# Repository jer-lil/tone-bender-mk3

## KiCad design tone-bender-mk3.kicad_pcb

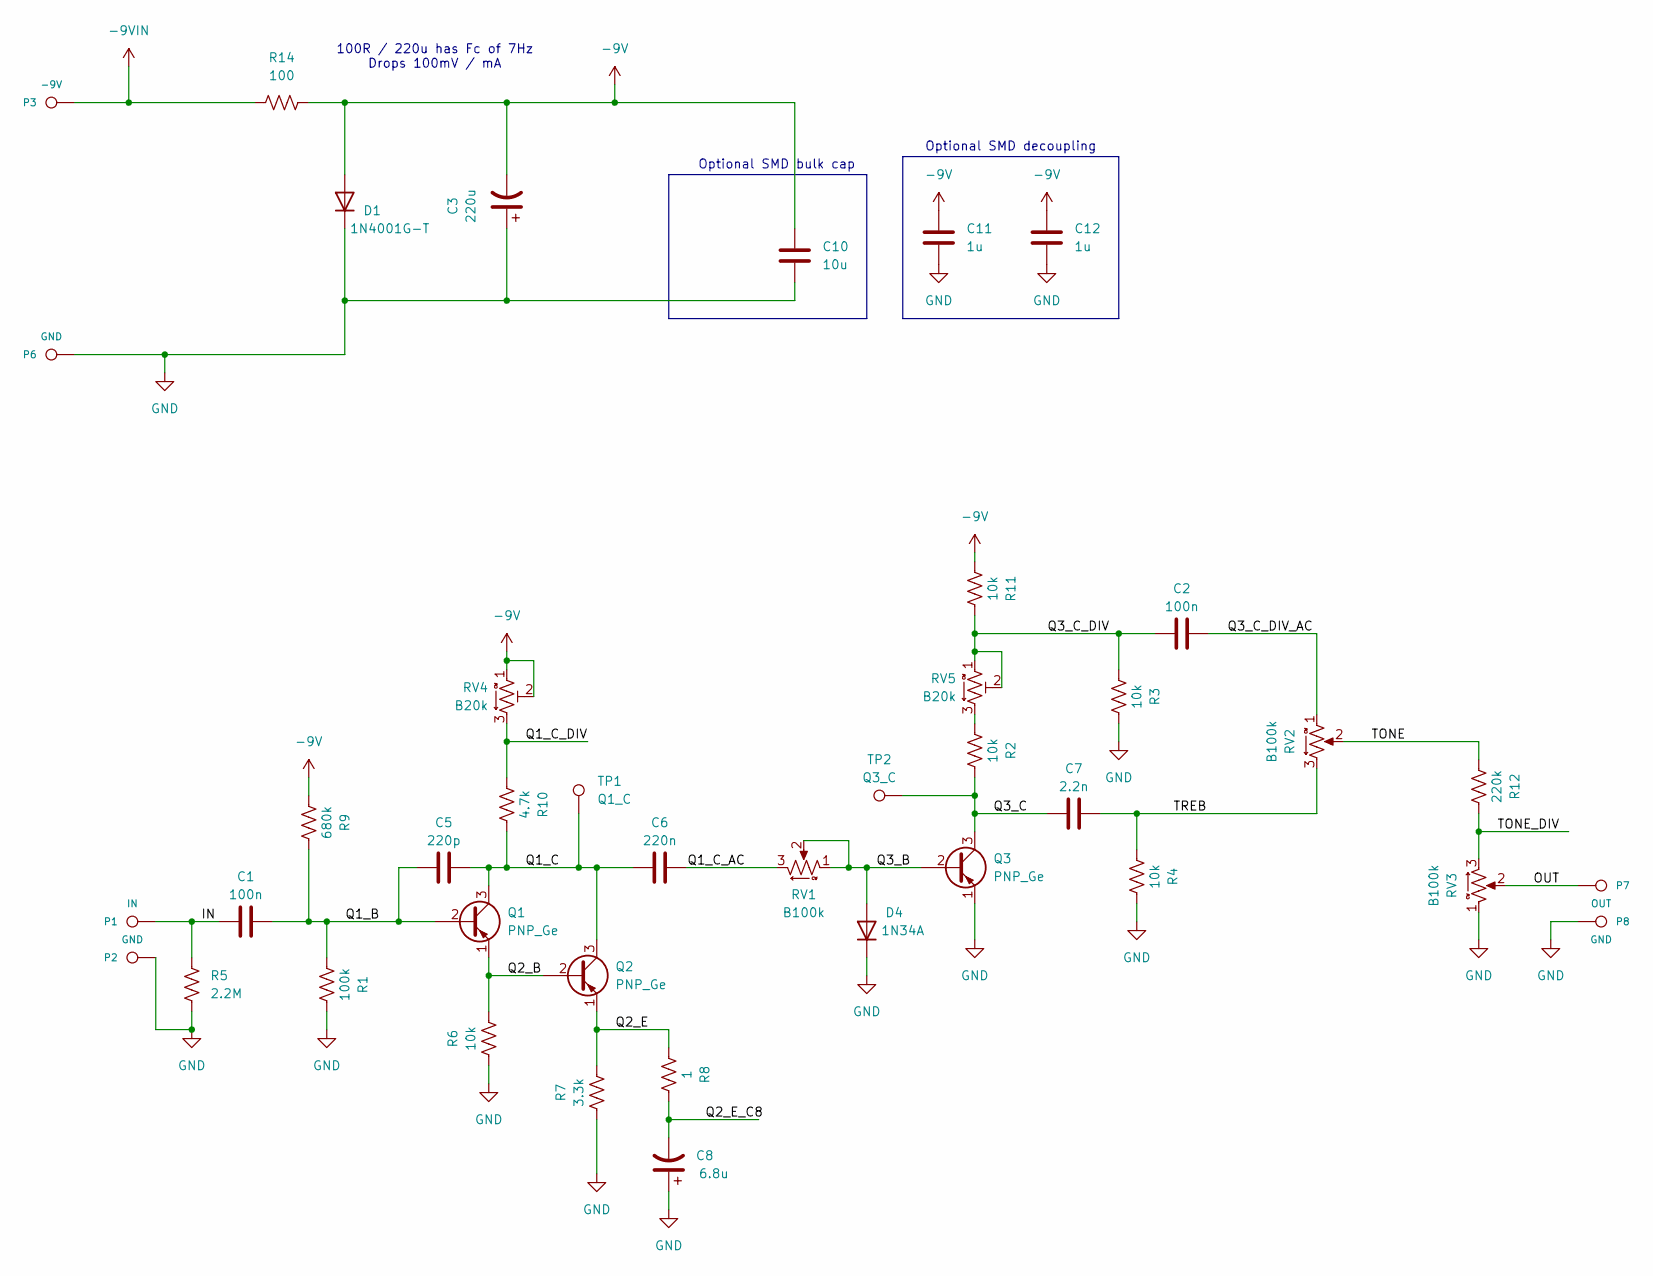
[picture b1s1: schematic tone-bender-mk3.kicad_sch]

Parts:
C1, C2: 100n; C_Rect_L7.2mm_W5.5mm_P5.00mm_FKS2_FKP2_MKS2_MKP2; Tolerance 20%
C3: 220u; CP_Radial_D8.0mm_P3.50mm
C5: 220p; C_Rect_L7.2mm_W4.5mm_P5.00mm_FKS2_FKP2_MKS2_MKP2; Tolerance 20%
C6: 220n; C_Rect_L7.2mm_W3.0mm_P5.00mm_FKS2_FKP2_MKS2_MKP2; Tolerance 20%
C7: 2.2n; C_Rect_L7.2mm_W4.5mm_P5.00mm_FKS2_FKP2_MKS2_MKP2; Tolerance 20%
C8: 6.8u; CP_Radial_D5.0mm_P2.50mm
C10: 10u; C_2220_5750Metric_Pad1.97x5.40mm_HandSolder
C11, C12: 1u; C_0805_2012Metric_Pad1.18x1.45mm_HandSolder
D1: 1N4001G-T; D_DO-41_SOD81_P7.5mm_Horizontal; Voltage 1V @ 1A; MPN 1N4001G-T
D4: 1N34A; D_DO-41_SOD81_P10.0mm_Horizontal; Voltage 0.3V; MPN 1N34A
P1: IN; WirePad_22AWG
P2, P6, P8: GND; WirePad_22AWG
P3: -9V; WirePad_22AWG
P7: OUT; WirePad_22AWG
Q1, Q2, Q3: PNP_Ge; TO-92L_Wide_EBC; MPN PNP_Ge
R1: 100k; R_Axial_DIN0207_L6.3mm_D2.5mm_P7.5mm_Horizontal
R2, R3, R4, R6, R11: 10k; R_Axial_DIN0207_L6.3mm_D2.5mm_P7.5mm_Horizontal
R5: 2.2M; R_Axial_DIN0207_L6.3mm_D2.5mm_P7.5mm_Horizontal
R7: 3.3k; R_Axial_DIN0207_L6.3mm_D2.5mm_P7.5mm_Horizontal
R8: 1; R_Axial_DIN0207_L6.3mm_D2.5mm_P7.5mm_Horizontal
R9: 680k; R_Axial_DIN0207_L6.3mm_D2.5mm_P7.5mm_Horizontal
R10: 4.7k; R_Axial_DIN0207_L6.3mm_D2.5mm_P7.5mm_Horizontal
R12: 220k; R_Axial_DIN0207_L6.3mm_D2.5mm_P7.5mm_Horizontal
R14: 100; R_Axial_DIN0207_L6.3mm_D2.5mm_P7.5mm_Horizontal
RV1, RV2, RV3: B100k; Potentiometer_16MM
RV4, RV5: B20k; Potentiometer_Bourns_3362P_Vertical; MPN 3362P-1-203LF
TP1: Q1_C; TestPoint_Keystone_5000-5004_Miniature
TP2: Q3_C; TestPoint_Keystone_5000-5004_Miniature

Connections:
-9V: C3.2, C10.1, C11.1, C12.1, D1.2 (A), R9.2, R11.2, R14.2, RV4.1, RV4.2
-9VIN: P3.1, R14.1
/IN: C1.1, P1.1, R5.1
/OUT: P7.1, RV3.2
/Q1_B: C1.2, C5.1, Q1.2 (B), R1.2, R9.1
/Q1_C: C5.2, C6.1, Q1.3 (C), Q2.3 (C), R10.1, TP1.1
/Q1_C_AC: C6.2, RV1.3
/Q1_C_DIV: R10.2, RV4.3
/Q2_B: Q1.1 (E), Q2.2 (B), R6.1
/Q2_E: Q2.1 (E), R7.1, R8.2
/Q2_E_C8: C8.2, R8.1
/Q3_B: D4.2 (A), Q3.2 (B), RV1.1, RV1.2
/Q3_C: C7.1, Q3.3 (C), R2.1, TP2.1
/Q3_C_DIV: C2.1, R3.2, R11.1, RV5.1, RV5.2
/Q3_C_DIV_AC: C2.2, RV2.1
/TONE: R12.2, RV2.2
/TONE_DIV: R12.1, RV3.3
/TREB: C7.2, R4.2, RV2.3
GND: C3.1, C8.1, C10.2, C11.2, C12.2, D1.1 (K), D4.1 (K), P2.1, P6.1, P8.1, Q3.1 (E), R1.1, R3.1, R4.1, R5.2, R6.2, R7.2, RV3.1
unnamed: R2.2, RV5.3

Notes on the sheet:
100R / 220u has Fc of 7Hz Drops 100mV / mA
Optional SMD bulk cap
Optional SMD decoupling

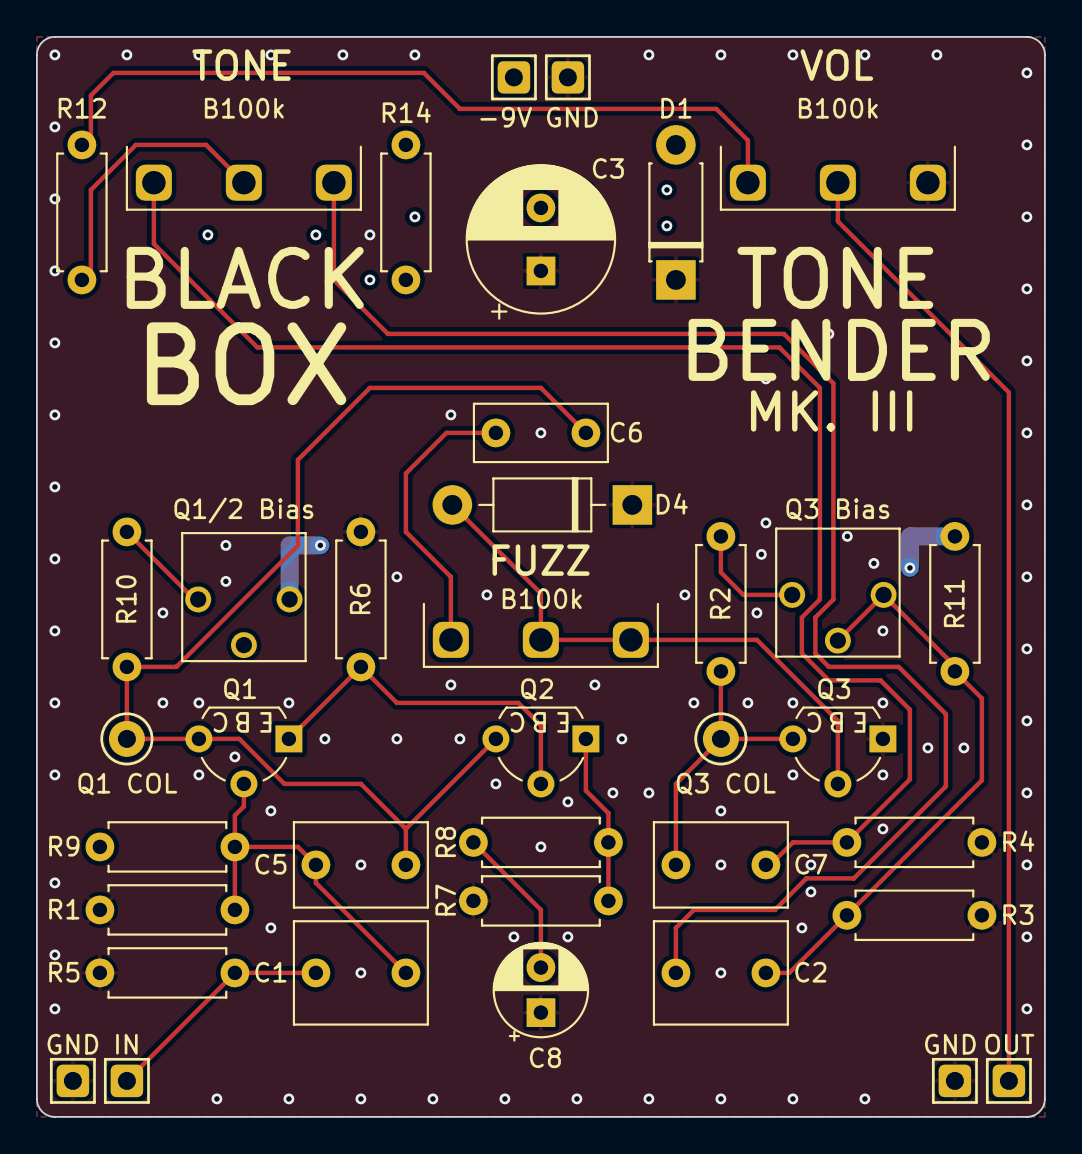
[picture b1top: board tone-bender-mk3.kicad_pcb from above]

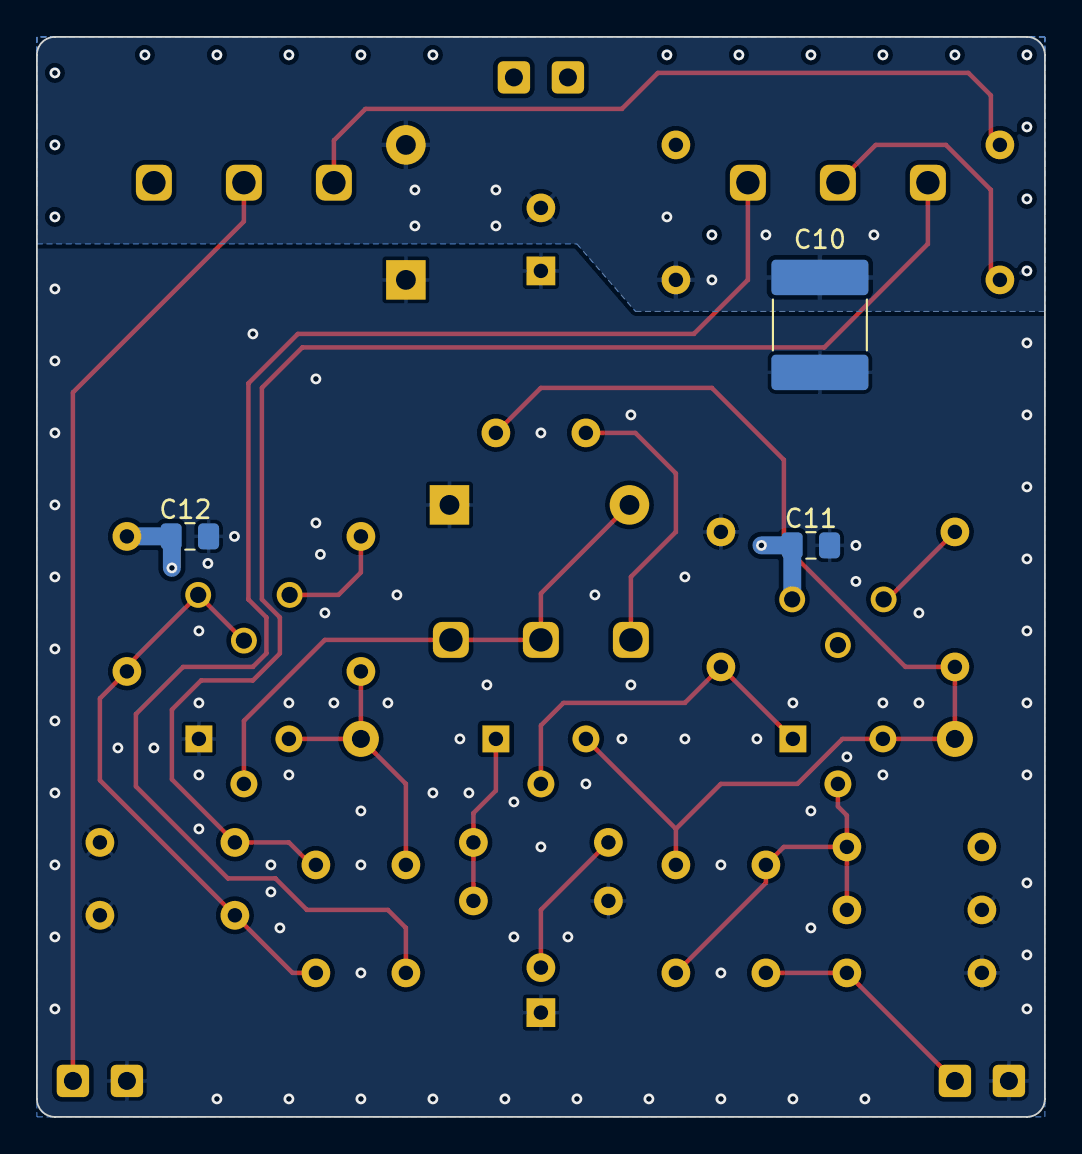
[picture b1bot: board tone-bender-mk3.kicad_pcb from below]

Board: 4 copper layers, 56.0 x 60.0 mm, 41 parts (6 on the bottom side), 20 nets.

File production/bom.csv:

Designator,Footprint,Quantity,Value,LCSC Part #
"C1, C2",C_Rect_L7.2mm_W5.5mm_P5.00mm_FKS2_FKP2_MKS2_MKP2,2,100n,
C10,2220,1,10u,
"C11, C12",0805,2,1u,
C3,CP_Radial_D8.0mm_P3.50mm,1,220u,
C5,C_Rect_L7.2mm_W4.5mm_P5.00mm_FKS2_FKP2_MKS2_MKP2,1,220p,
C6,C_Rect_L7.2mm_W3.0mm_P5.00mm_FKS2_FKP2_MKS2_MKP2,1,220n,
C7,C_Rect_L7.2mm_W4.5mm_P5.00mm_FKS2_FKP2_MKS2_MKP2,1,2.2n,
C8,CP_Radial_D5.0mm_P2.50mm,1,6.8u,
D1,D_DO-41_SOD81_P7.5mm_Horizontal,1,1N4001G-T,1N4001G-T
D4,D_DO-41_SOD81_P10.0mm_Horizontal,1,1N34A,1N34A
P1,WirePad_22AWG,1,IN,
"P2, P6, P8",WirePad_22AWG,3,GND,
P3,WirePad_22AWG,1,-9V,
P7,WirePad_22AWG,1,OUT,
"Q1, Q2, Q3",TO-92L_Wide_EBC,3,PNP_Ge,PNP_Ge
R1,R_Axial_DIN0207_L6.3mm_D2.5mm_P7.5mm_Horizontal,1,100k,
R10,R_Axial_DIN0207_L6.3mm_D2.5mm_P7.5mm_Horizontal,1,4.7k,
"R11, R2, R3, R4, R6",R_Axial_DIN0207_L6.3mm_D2.5mm_P7.5mm_Horizontal,5,10k,
R12,R_Axial_DIN0207_L6.3mm_D2.5mm_P7.5mm_Horizontal,1,220k,
R14,R_Axial_DIN0207_L6.3mm_D2.5mm_P7.5mm_Horizontal,1,100,
R5,R_Axial_DIN0207_L6.3mm_D2.5mm_P7.5mm_Horizontal,1,2.2M,
R7,R_Axial_DIN0207_L6.3mm_D2.5mm_P7.5mm_Horizontal,1,3.3k,
R8,R_Axial_DIN0207_L6.3mm_D2.5mm_P7.5mm_Horizontal,1,1,
R9,R_Axial_DIN0207_L6.3mm_D2.5mm_P7.5mm_Horizontal,1,680k,
"RV1, RV2, RV3",Potentiometer_16MM,3,B100k,
"RV4, RV5",Potentiometer_Bourns_3362P_Vertical,2,B20k,3362P-1-203LF
TP1,TestPoint_Keystone_5000-5004_Miniature,1,Q1_C,
TP2,TestPoint_Keystone_5000-5004_Miniature,1,Q3_C,

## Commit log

2024-04-29 Adding files
    might not want fuzz-backups folder, not sure what that is
2024-04-29 Moved and renamed files
2024-04-29 Finished schematic ish, added some footprints
2024-04-29 deleted old backups folder
2024-05-22 donezo
    exporting for quote now
2024-05-22 Couple of tweaks
    Rounded corners, made vias 0.3mm diameter hole
2024-05-22 Added gnd pour to top layer
2024-05-22 file cleanup and backup zips
    no real changes
2025-04-10 Adding gitignore and interactive BOM
2025-04-10 Removing files added to gitignore
2025-04-10 rename bom folder to docs for gh pages
